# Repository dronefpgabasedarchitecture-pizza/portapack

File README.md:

portapack
=========

Portable software-defined radio add-on for HackRF Jawbreaker

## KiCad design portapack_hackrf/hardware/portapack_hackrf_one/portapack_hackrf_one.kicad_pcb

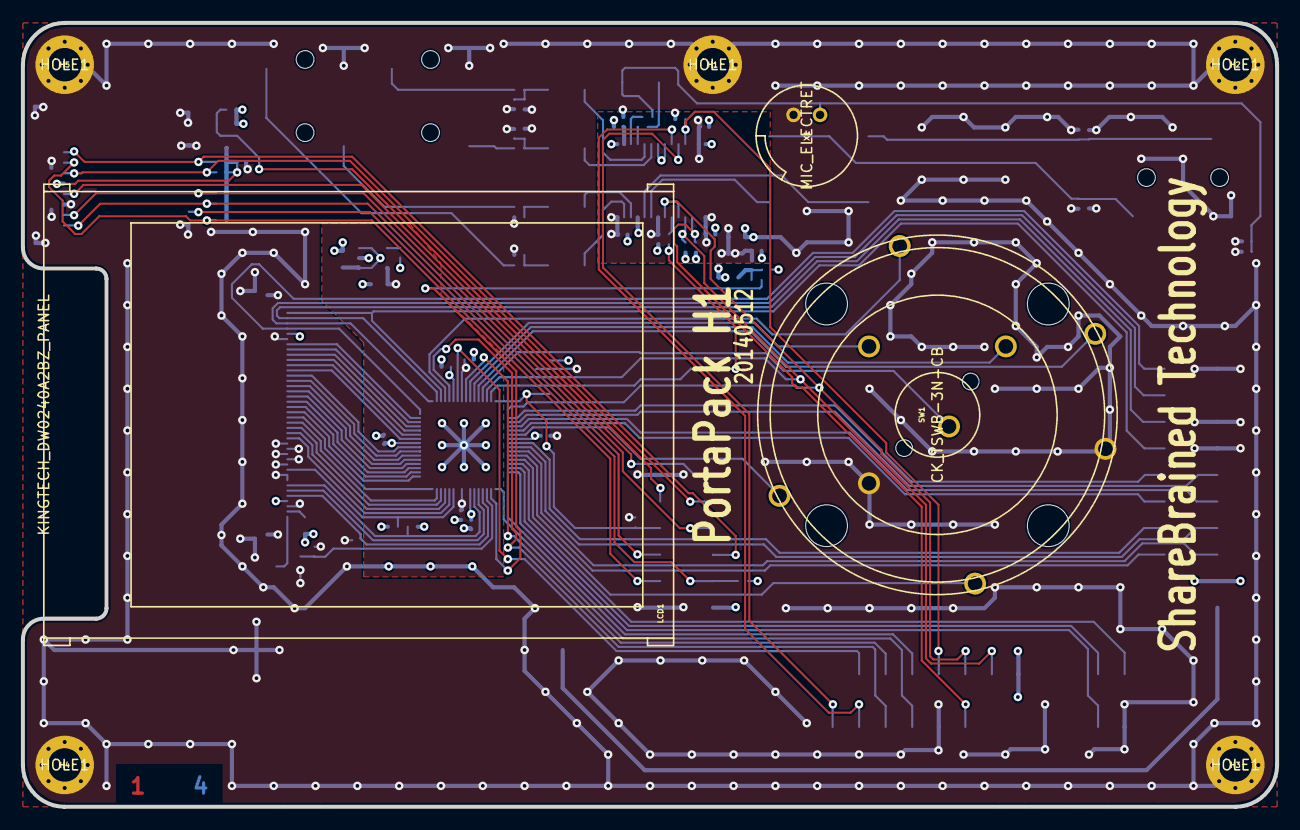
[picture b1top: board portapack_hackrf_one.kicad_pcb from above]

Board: 4 copper layers, 120.0 x 75.0 mm, 92 parts (0 on the bottom side), 100 nets.

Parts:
BT1: BATTERY; MPD_BU2032SM-BT-G
C1, C2: 220U; IPC_CAPAE830X620N
C3, C11, C12: 1U; IPC_CAPAE430X540N
C4, C5, C6, C9, C10: 220P; IPC_CAPC1005X55N
C7, C15, C16, C18, C19, C20, C21, C22, C24, C25, C26, C28, C29, C30: 100N; IPC_CAPC1005X55N
C8, C27: 10U; IPC_CAPC1608X95N
C13, C14: 10U; IPC_CAPAE430X540N
C17: 1U; IPC_CAPC1608X95N
C23: DNI; IPC_CAPC1005X55N
H1, H2, H3, H4, H5: HOLE1; HOLE_3200UM_VIAS
J2: MICROSD_DETSW; ALPS_SCHA4B0400
J3: KINGTECH_DW0240A2BZ_FPC; MOLEX_54132-40XX_LR
LCD1: KINGTECH_DW0240A2BZ_PANEL
P1: TRRS_SW_JACK; CUI_SJ-43516-SMT
P2, P3: TRS_JACK; CUI_SJ-3524-SMT
P20: HACKRF_ONE_P20; HEADER_11X2_REV_SM_254
P22: HACKRF_ONE_P22; HEADER_13X2_REV_SM_254
P28: HACKRF_ONE_P28; HEADER_11X2_REV_SM_254
Q1, Q2: MOSFET_P; IPC_SOT95P240X110-3N
Q3: MOSFET_N; IPC_SOT95P230X110-3N
R1: R; IPC_RESC1005X40N
R2, R3, R4, R17, R18: 47K; IPC_RESC1005X40N
R5: 680R; IPC_RESC1005X40N
R6, R12, R13, R14, R15, R16, R19, R20, R23, R24, R25, R27, R28, R29, R31, R32, R33: 10K; IPC_RESC1005X40N
R7, R8, R10, R11: 5K6; IPC_RESC1005X40N
R9: 100K; IPC_RESC1005X40N
R21, R22, R26: 100R; IPC_RESC1005X40N
R30: R; IPC_RESC1608X55N
SW1: CK_TSWB-3N-CB; CK_TSWB-3N-CB222_LFS
TP1, TP2, TP3, TP4, TP5, TP6: TP; TP_1MM
U1: 5M40ZE64; IPC_QFP40P900X900X120-65N
U2: REGULATOR_SOT23_5; IPC_SOT95P280X110-5N
U3: WM8731SEDS; IPC_SOP65P780X200-28N
X1: MIC_ELECTRET; CUI_CMA-4544PF-W

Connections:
+1.8V: C22.1, C26.1, C27.1, U1.8, U1.41, U2.5
+3.3V: C16.1, C17.1, C18.1, C20.1, C21.1, J3.4, J3.36, P20.3, P22.11, P28.1, Q1.2, Q2.2, R9.1, R13.1, R23.1, R28.1, R29.1, R30.1, TP6.1, U1.6, U1.23, U1.39, U1.57, U2.1, U2.3
/CODEC_ENABLE#: R6.2, U1.34
/CODEC_VDD: C7.1, C8.1, C19.1, C24.2, C25.1, C28.2, Q1.3, R12.1, U3.1, U3.8, U3.14, U3.27
/CPLD_TDI: P28.19, R26.2, TP2.1, U1.15
/GPIO3_8: P20.5, U1.26
/GPIO3_9: P20.6, U1.27
/GPIO3_10: P20.7, U1.25
/GPIO3_11: P20.8, U1.24
/GPIO3_12: P20.9, U1.20
/GPIO3_13: P20.10, U1.21
/GPIO3_14: P20.11, U1.19
/GPIO3_15: P20.12, U1.18
/I2S0_MCLK: P22.17, R31.1, U3.25
/I2S0_RX_SDA: R26.1, U3.6
/I2S0_SCK: P22.16, R24.1, U3.3
/I2S0_TX_SDA: P22.13, R25.1, TP1.1, U1.14, U3.4
/I2S0_WS: P22.15, TP4.1, U1.17, U3.5, U3.7
/LCD_BACKLIGHT: Q3.1, R27.1, U1.35
/LCD_DB0: J3.33, U1.62
/LCD_DB1: J3.32, U1.61
/LCD_DB2: J3.31, U1.60
/LCD_DB3: J3.30, U1.59
/LCD_DB4: J3.29, U1.58
/LCD_DB5: J3.28, U1.56
/LCD_DB6: J3.27, U1.55
/LCD_DB7: J3.26, U1.54
/LCD_DB8: J3.25, U1.53
/LCD_DB9: J3.24, U1.52
/LCD_DB10: J3.23, U1.51
/LCD_DB11: J3.22, U1.50
/LCD_DB12: J3.21, U1.49
/LCD_DB13: J3.20, U1.48
/LCD_DB14: J3.19, U1.47
/LCD_DB15: J3.18, U1.46
/LCD_DB16: J3.17, U1.45
/LCD_DB17: J3.16, U1.44
/LCD_RD#: J3.7, R29.2, U1.38
/LCD_RESET#: J3.5, R33.1, U1.36
/LCD_RS: J3.6, U1.37
/LCD_TE: J3.34, U1.63
/LCD_WR#: J3.10, R28.2, U1.43
/LHPOUT: C1.1, U3.9
/LLINEIN: C11.1, U3.20
/LOUT: C13.1, U3.12
/MICBIAS: C30.1, R5.1, U3.17
/MICIN: R1.2, U3.18
/P1_8: P28.8, R32.1, TP3.1, U1.16
/P2_3: P22.6, U1.31
/P2_4: P22.5, U1.30
/P2_8: P22.23, U1.7
/P2_9: P22.21, U1.9
/P2_13: P22.22, U1.5
/RESET#: P22.3, U1.29
/RHPOUT: C2.1, U3.10
/RLINEIN: C12.1, U3.19
/ROUT: C14.1, U3.13
/SCL: P22.26, U3.24
/SDA: P22.24, U3.23
/SD_CD: J2.A, P28.3, R13.2
/SD_CLK: J2.5, P28.11
/SD_CMD: J2.3, P28.9, R16.2
/SD_DAT0: J2.7, P28.7, R15.2
/SD_DAT1: J2.8, P28.6, R14.2
/SD_DAT2: J2.1, P28.5, R20.2
/SD_DAT3: J2.2, P28.4, R19.2
/SD_POW: P28.10, Q2.1, R23.2
/SW_D: SW1.S2, U1.12
/SW_L: SW1.S5, U1.28
/SW_R: SW1.S3, U1.4
/SW_ROT_A: SW1.A, U1.11
/SW_ROT_B: SW1.B, U1.10
/SW_SEL: SW1.S1, U1.13
/SW_U: SW1.S4, U1.22
/TP_D: J3.38, P20.18, U1.1
/TP_L: J3.39, P20.16, U1.2
/TP_R: J3.37, P20.20, U1.64
/TP_U: J3.40, P20.14, U1.3
/U0_RXD: P22.19, U1.32
/U0_TXD: P22.20, U1.33
/VBAT: BT1.1, P20.1
GND: BT1.2, C4.1, C5.2, C6.2, C8.2, C9.1, C10.2, C15.2, C16.2, C17.2, C18.2, C19.2, C20.2, C21.2, C22.2, C23.2, C24.1, C25.2, C26.2, C27.2, C28.1, C29.2, C30.2, H1.1, H2.1, H3.1, H4.1, H5.1, J2.0, J2.6, J2.B, J2.SH, J3.3, J3.8, J3.9, J3.11, J3.12, J3.13, J3.14, J3.15, J3.35, J3.SHLD, P1.4, P2.1, P3.1, P20.13, P20.15, P20.19, P22.4, P22.10, P22.18, P28.2, P28.12, Q3.2, R2.1, R3.2, R4.2, R10.1, R11.2, R12.2, R17.1, R18.2, R24.2, R25.2, R27.2, R31.2, R32.2, R33.2, SW1.CA, SW1.CB, TP5.1, U1.65, U2.2, U3.11, U3.15, U3.21, U3.22, U3.28, X1.2
unnamed: C1.2, C4.2, P1.2, R2.2
unnamed: C2.2, C5.1, P1.3, R3.1
unnamed: C3.1, R1.1
unnamed: C3.2, C6.1, P1.1, R4.1, R5.2, X1.1
unnamed: C7.2, Q1.1, R6.1, R9.2
unnamed: C10.1, C12.2, R8.1, R11.1
unnamed: C9.2, C11.2, R7.1, R10.2
unnamed: C13.2, R17.2, R21.2
unnamed: C14.2, R18.1, R22.2
unnamed: C15.1, J2.4, Q2.3, R14.1, R15.1, R16.1, R19.1, R20.1
unnamed: C23.1, U2.4
unnamed: C29.1, U3.16
unnamed: J3.1, Q3.3
unnamed: J3.2, R30.2
unnamed: P2.2, R7.2
unnamed: P2.3, R8.2
unnamed: P3.2, R21.1
unnamed: P3.3, R22.1

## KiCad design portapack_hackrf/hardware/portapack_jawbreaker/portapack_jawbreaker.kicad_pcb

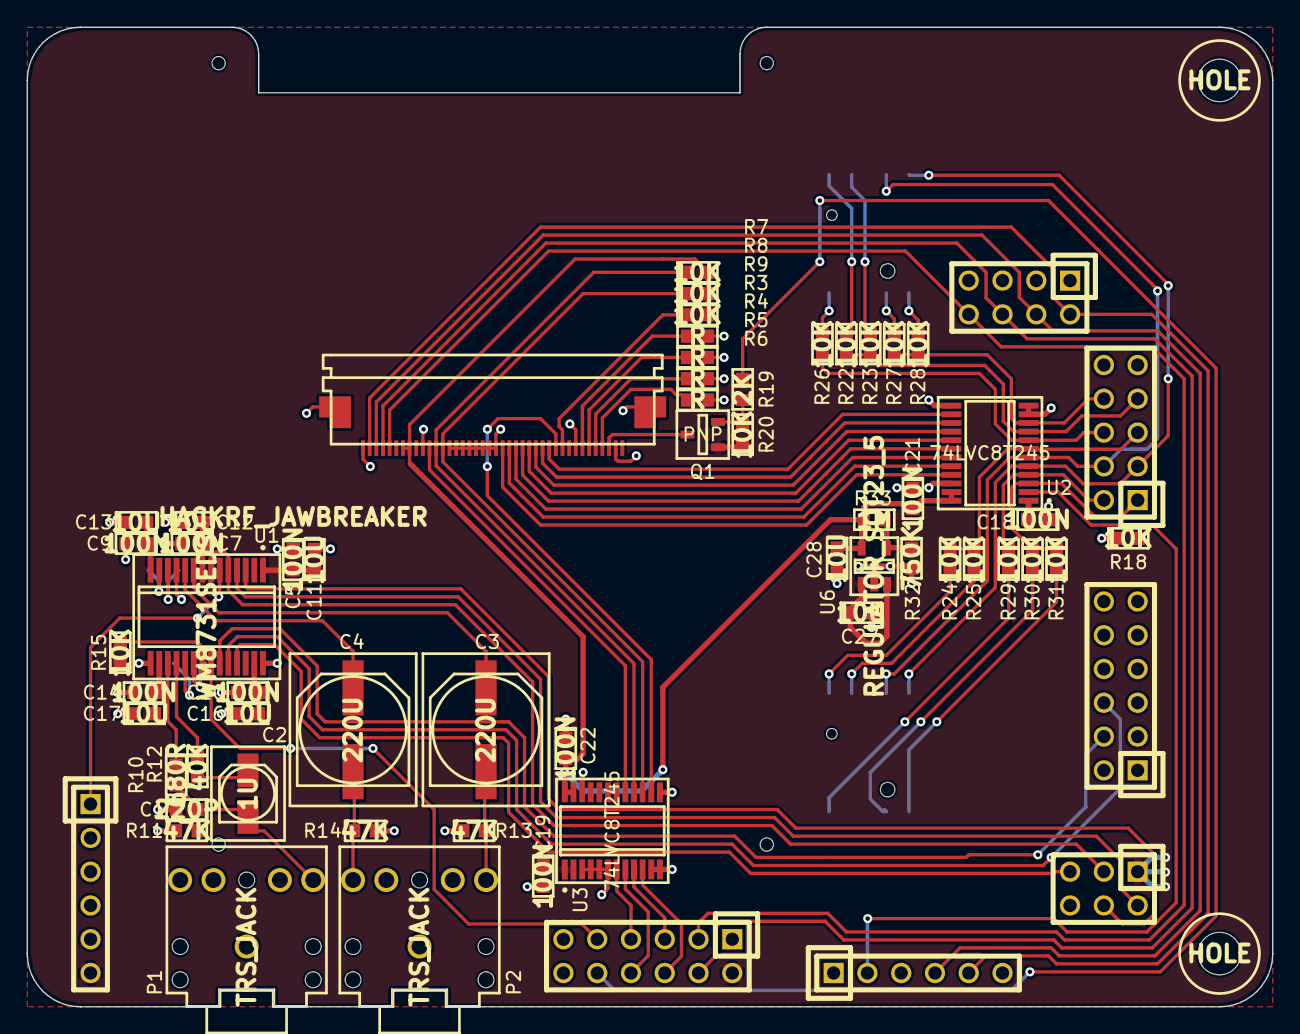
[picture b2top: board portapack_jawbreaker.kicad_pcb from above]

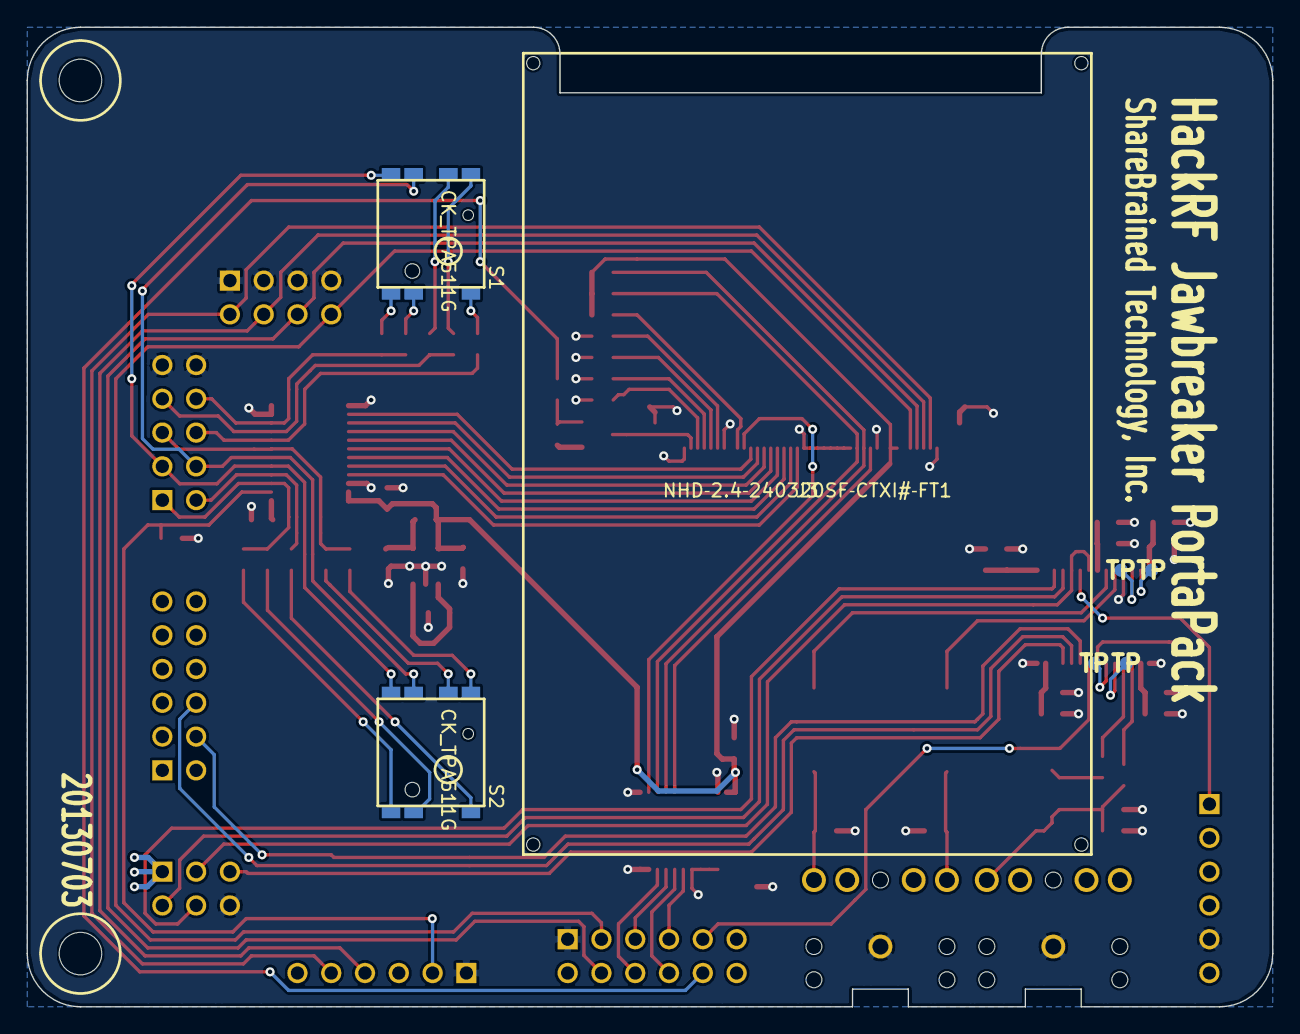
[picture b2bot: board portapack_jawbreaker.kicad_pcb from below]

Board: 2 copper layers, 93.7 x 73.7 mm, 65 parts (7 on the bottom side), 73 nets.

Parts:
C1: 220P; IPC_CAPC1608X90N
C2: 1U; IPC_CAPAE430X540N
C3, C4: 220U; IPC_CAPAE830X620N
C5, C7, C9, C10, C14, C18, C19, C21, C22: 100N; IPC_CAPC1608X90N
C11, C12, C13, C16, C17, C27, C28: 10U; IPC_CAPC1608X95N
H1, H2: HOLE; HOLE_3P2MM
J1: HACKRF_JAWBREAKER; HACKRF_JAWBREAKER_SHIELD
J3: NHD‐2.4‐240320SF‐CTXI#‐FT1; NHD-2.4-240320SF-CTXI-FT1
P1, P2: TRS_JACK; CUI_SJ1-352XN
Q1: PNP; IPC_SOT95P237X111-3N
R3, R4, R5, R6: R; IPC_RESC1608X55N
R7, R8, R9, R15, R18, R20, R22, R23, R24, R25, R26, R27, R28, R29, R30, R31: 10K; IPC_RESC1608X55N
R10: 680R; IPC_RESC1608X55N
R11, R13, R14: 47K; IPC_RESC1608X55N
R12: 40K; IPC_RESC1608X55N
R19: 2K; IPC_RESC1608X55N
R32: 750K; IPC_RESC1608X55N
R33: 1M; IPC_RESC1608X55N
S1, S2: CK_TPA511G
TP1, TP2, TP3, TP4: TP; TP_1MM
U1: WM8731SEDS; IPC_SOP65P780X200-28N
U2, U3: 74LVC8T245; IPC_SOP65P640X120-24N
U6: REGULATOR_SOT23_5; IPC_SOT95P280X110-5N

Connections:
3V3: C5.1, C7.1, C9.1, C10.1, C11.1, C12.1, C13.1, C16.1, C18.1, C19.1, C27.1, J1.2201, J1.2802, J1.2906, Q1.1, R15.2, R20.2, U1.1, U1.8, U1.14, U1.27, U2.1, U3.1, U3.2, U6.1, U6.3
/GPIO0: J1.2001, R30.2, R31.2, U2.3
/GPIO0_S: J3.22, U2.21
/GPIO1: J1.2002, R29.2, U2.4
/GPIO1_S: J3.23, U2.20
/GPIO2: J1.2003, S1.1, S2.1, U2.5
/GPIO2_S: J3.24, U2.19
/GPIO3: J1.2004, S1.2, S2.2, U2.6
/GPIO3_S: J3.25, U2.18
/GPIO4: J1.2005, R24.1, R25.1, U2.7
/GPIO4_S: J3.26, U2.17
/GPIO5: J1.2006, R26.2, U2.8
/GPIO5_S: J3.27, U2.16
/GPIO6: J1.2007, R22.1, R23.1, U2.9
/GPIO6_S: J3.28, U2.15
/GPIO7: J1.2008, R27.2, R28.2, U2.10
/GPIO7_S: J3.29, U2.14
/GPIO_DIR: J1.2502, R18.2, U2.2
/I2S0_RX_SDA: J1.2901, U1.6
/I2S0_TX_MCLK: J1.2205, U1.25
/I2S0_TX_SCK: J1.2204, U1.3
/I2S0_TX_SDA: J1.2202, U1.4
/I2S0_TX_WS: J1.2203, U1.5, U1.7
/LHPOUT: C3.1, U1.9
/MICBIAS: R10.2, U1.17
/MICIN: R12.2, U1.18
/RD#: J1.2805, U3.9
/RD#_S: J3.13, R8.1, U3.15
/RDY#: J1.2810, R19.1
/RESET#: J1.2806, U3.10
/RESET#_S: J3.30, U3.14
/RHPOUT: C4.1, U1.10
/RS: J1.2807, U3.7
/RS_S: J3.11, U3.17
/SPI_CS#_CODEC: J1.2809, U1.22
/SPI_MOSI: J1.1904, U1.23
/SPI_SCK: J1.1906, U1.24
/TS_X+: J1.2104, J1.2504, J3.3
/TS_X-: J1.2108, J1.2803, J3.5
/TS_Y+: J1.2106, J1.2804, J3.4
/TS_Y-: J1.2102, J1.2505, J3.2
/VCC_IO: C21.1, C22.1, C28.1, J3.7, J3.8, R7.2, R8.2, R9.2, R33.2, U2.23, U2.24, U3.23, U3.24, U6.5
/WR#: J1.2808, U3.8
/WR#_S: J3.12, R7.1, U3.16
GND: C1.2, C5.2, C7.2, C9.2, C10.2, C11.2, C12.2, C13.2, C14.2, C16.2, C17.2, C18.2, C19.2, C21.2, C22.2, C27.2, C28.2, J1.2009, J1.2010, J1.2101, J1.2103, J1.2105, J1.2107, J1.2206, J1.2501, J1.2801, J1.2905, J3.1, J3.10, J3.14, J3.15, J3.16, J3.17, J3.18, J3.19, J3.20, J3.21, J3.33, J3.39, J3.SHLD, P1.1, P2.1, R3.1, R4.1, R5.1, R6.1, R11.1, R13.2, R14.1, R18.1, R32.1, U1.11, U1.15, U1.28, U2.11, U2.12, U2.13, U2.22, U3.3, U3.4, U3.5, U3.6, U3.11, U3.12, U3.13, U3.22, U6.2
unnamed: TP3.1, U1.20
unnamed: TP1.1, U1.12
unnamed: TP2.1, U1.13
unnamed: TP4.1, U1.19
unnamed: R28.1, S1.4
unnamed: C1.1, C2.2, P1.2, R10.1, R11.2
unnamed: C2.1, R12.1
unnamed: C3.2, P2.2, R13.1
unnamed: R15.1, U1.21
unnamed: C4.2, P2.3, R14.2
unnamed: J3.31, R9.1
unnamed: C14.1, C17.1, U1.16
unnamed: Q1.2, R19.2, R20.1
unnamed: R31.1, S2.4
unnamed: J3.38, Q1.3
unnamed: R25.2, S2.6
unnamed: R30.1, S2.3
unnamed: R24.2, S2.7
unnamed: R26.1, S1.5
unnamed: R29.1, S2.5
unnamed: R22.2, S1.7
unnamed: R23.2, S1.6
unnamed: R27.1, S1.3
unnamed: R32.2, R33.1, U6.4
unnamed: J3.35, R4.2
unnamed: J3.36, R5.2
unnamed: J3.37, R6.2
unnamed: J3.34, R3.2

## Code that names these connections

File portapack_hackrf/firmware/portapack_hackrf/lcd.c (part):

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#include "lcd.h"
#include "font_fixed_8x16.h"

#define RDY_N_PORT (GPIO1)
#define RDY_N_PIN (8)
#define RDY_N_BIT (1 << RDY_N_PIN)

#define SPI_CS_N_CODEC_PORT (GPIO1)
#define SPI_CS_N_CODEC_PIN (9)
#define SPI_CS_N_CODEC_BIT (1 << SPI_CS_N_CODEC_PIN)

#define WR_N_PORT (GPIO1)
#define WR_N_PIN (1)
#define WR_N_BIT (1 << WR_N_PIN)

#define RS_PORT (GPIO1)
#define RS_PIN (2)
#define RS_BIT (1 << RS_PIN)

#define RESET_N_PORT (GPIO1)
#define RESET_N_PIN (3)
#define RESET_N_BIT (1 << RESET_N_PIN)

#define RD_N_PORT (GPIO1)
#define RD_N_PIN (4)
#define RD_N_BIT (1 << RD_N_PIN)

#define TS_Y_P_PORT (GPIO1)
#define TS_Y_P_PIN (5)
#define TS_Y_P_BIT (1 << TS_Y_P_PIN)

#define TS_X_N_PORT (GPIO1)
#define TS_X_N_PIN (6)
#define TS_X_N_BIT (1 << TS_X_N_PIN)

#define TS_X_P_PORT (GPIO5)
#define TS_X_P_PIN (1)
#define TS_X_P_BIT (1 << TS_X_P_PIN)

#define TS_Y_N_PORT (GPIO5)
#define TS_Y_N_PIN (0)
#define TS_Y_N_BIT (1 << TS_Y_N_PIN)

#define DATA_DIR_PORT (GPIO0)
#define DATA_DIR_PIN (7)
#define DATA_DIR_BIT (1 << DATA_DIR_PIN)

#define DATA_BYTE_PORT (GPIO3)
#define DATA_BYTE_LSB_PIN (8)
#define DATA_BYTE_MASK (0xff << DATA_BYTE_LSB_PIN)

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}

void lcd_dir_read() {
	GPIO_DIR(GPIO3) &= ~(0xffL << 8);
	lcd_dir(0);
}

void lcd_dir_write() {
	lcd_dir(1);
	GPIO_DIR(GPIO3) |= (0xffL << 8);
}

void lcd_dir_idle() {
	lcd_dir(1);
	GPIO_DIR(GPIO3) &= ~(0xffL << 8);
}

void lcd_rs(const uint_fast8_t value) {
	MMIO32(GPIO_W34) = value;
}

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	lcd_dir_read();
	lcd_rd_n(0);
	delay(100);
	const uint_fast8_t value = (GPIO3_PIN >> 8) & 0xff;
	lcd_rd_n(1);
	lcd_dir_idle();
	
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	// Discharge all pins before changing to inputs for reading.
	GPIO3_MPIN = 0 << 8;

	GPIO_DIR(GPIO3) &= ~(0xffL << 8);
	GPIO_DIR(GPIO3) |= (1 << (3 + 8)) | (1 << (2 + 8));

	MMIO32(GPIO_W107) = 0;
	MMIO32(GPIO_W106) = 1;	// GPIO2 reads LEFT/DOWN/SELECT
	delay(100);
	uint32_t data = (GPIO3_MPIN >> 8) & 0xff;
	// GPIO7: S1.DOWN
	// GPIO6: S1.LEFT
	// GPIO5: S1.SELECT
	// GPIO4: S2.LEFT
	// GPIO1: S2.SELECT
	// GPIO0: S2.DOWN

	MMIO32(GPIO_W106) = 0;
	MMIO32(GPIO_W107) = 1;	// GPIO3 reads RIGHT/UP
	delay(100);
	data |= GPIO3_MPIN & 0xff00;
	// GPIO7: S1.UP
	// GPIO6: S1.RIGHT
	// GPIO4: S2.RIGHT
	// GPIO0: S2.UP

	MMIO32(GPIO_W107) = 0;
	
	GPIO_DIR(GPIO3) |= (0xffL << 8);

	return data;
}
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	
	//gpio_set(RDY_N_PORT, RDY_N_PIN);
	lcd_backlight_n(1);
	GPIO_DIR(RDY_N_PORT) |= RDY_N_BIT;
	/*
	gpio_set(SPI_CS_N_CODEC_PORT, SPI_CS_N_CODEC_PIN);
	GPIO_DIR(SPI_CS_N_CODEC_PORT) |= SPI_CS_N_CODEC_BIT;
	*/
	//gpio_set(WR_N_PORT, WR_N_PIN);
	lcd_wr_n(1);
	GPIO_DIR(WR_N_PORT) |= WR_N_BIT;
	
	gpio_clear(RS_PORT, RS_PIN);
	GPIO_DIR(RS_PORT) |= RS_BIT;
	
	//gpio_clear(RESET_N_PORT, RESET_N_PIN);
	lcd_reset_n(0);
	GPIO_DIR(RESET_N_PORT) |= RESET_N_BIT;
	
	//gpio_set(RD_N_PORT, RD_N_PIN);
	lcd_rd_n(1);
	GPIO_DIR(RD_N_PORT) |= RD_N_BIT;
	
	//GPIO_DIR(TS_Y_P_PORT) |= TS_Y_P_BIT;
	//GPIO_DIR(TS_X_N_PORT) |= TS_X_N_BIT;
	
	//scu_pinmux(SCU_PINMUX_CPLD_TMS, (SCU_CONF_FUNCTION3));	// I2S0_RX_SDA
	
	scu_pinmux(SCU_PINMUX_U0_TXD, (SCU_GPIO_NOPULL | SCU_CONF_FUNCTION4));
	scu_pinmux(SCU_PINMUX_U0_RXD, (SCU_GPIO_NOPULL | SCU_CONF_FUNCTION4));
	scu_pinmux(SCU_PINMUX_ISP, (SCU_GPIO_NOPULL | SCU_CONF_FUNCTION0));

	//GPIO_DIR(TS_X_P_PORT) |= TS_X_P_BIT;
	//GPIO_DIR(TS_Y_N_PORT) |= TS_Y_N_BIT;
	
	//gpio_clear(DATA_DIR_PORT, DATA_DIR_PIN);
	lcd_dir_read();
	GPIO3_MASK = ~(0xffU << 8);
	GPIO_DIR(DATA_DIR_PORT) |= DATA_DIR_BIT;
	/*
	scu_pinmux(SCU_PINMUX_I2S0_TX_SDA, (SCU_CONF_FUNCTION0));
	scu_pinmux(SCU_PINMUX_I2S0_TX_WS, (SCU_CONF_FUNCTION0));
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	scu_pinmux(SCU_PINMUX_GPIO3_14, (SCU_GPIO_NOPULL | SCU_CONF_FUNCTION0));
	scu_pinmux(SCU_PINMUX_GPIO3_15, (SCU_GPIO_NOPULL | SCU_CONF_FUNCTION0));
	
	GPIO_DIR(DATA_BYTE_PORT) &= ~(DATA_BYTE_MASK);
	/*
	scu_pinmux(SCU_SSP0_SCK, (SCU_CONF_FUNCTION1));		// SPI
	scu_pinmux(SCU_SSP0_MOSI, (SCU_CONF_FUNCTION1));	// SPI	
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
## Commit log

2014-01-01 Committed 20130703_1525 schematic/PCB/Gerbers of Jawbreaker PortaPack.
2014-01-01 HackRF PortaPack code in progress. Remnants of the spectrum analyzer code and VFD code are present and need a better home.
2014-01-01 Basic .gitignore.
2014-01-01 Fix breakage from incomplete change in decimation and demodulation API arguments.
2014-01-01 Finish/unbreak change to processing loop metrics variable names.
2014-01-01 Remove unused variable.
2014-01-01 Disable unfinished narrowband FM processing function.
2014-01-01 Document WBFM audio filter/decimator.
2014-01-01 Clean up call arguments within FM broadcast demodulation function.
2014-01-01 Add TODO to implement FM broadcast channel filter for improved adjacent channel rejection.
2014-01-01 Clean up comments in baseband processing.
2014-01-01 Clean up decimation API arguments.
2014-01-01 Move decimation functions into decimate.*. Clean up decimation APIs a bit more. Remove junk decimation functions.
2014-01-01 Quick and dirty NBFM receive support. Receives NOAA WX radio well, but could certainly use a channel filter and other tweaks.
2014-01-01 Remove dead code/comment.
2014-01-01 Remove a bit more dead code. I'm committed to using the fixed-point atan2() at this point.
2014-01-01 Extract a few complex math functions.
2014-01-01 Remove gr_fast_atan2f from code. TODO to implement FM demodulation gain correction.
2014-01-01 Clean up and rename demodulation APIs a bit more.
2014-01-01 Add AM receiver code.
2014-01-01 More decimation function renaming...
2014-01-01 Generalize FIR real filter a bit, extract filter taps into application code.
2014-01-01 Massive rework of LCD layer, refactored a bunch of stuff.
2014-01-02 Define some color constants.
2014-01-02 Reformat default color values to be a bit more verbose.
2014-01-02 Fix LCD font pixel scan order.
2014-01-02 Add function to compute string pixel width based on current font.
2014-01-02 Tweak lcd_draw_string() to support variable-width characters in a font.
2014-01-02 Nuke residual spectrum analyzer code that will need serious upgrading to work with new frameworks.
2014-01-02 Add bigger, 8x16 fixed font, make the default.
2014-01-02 Clean up application tuning functions.
2014-01-02 Add LCD field drawing functions.
2014-01-02 Relocate baseband sample buffers to make a 32K block for the M0. Relocate shared memory items to new M0 region.
2014-01-02 Create device_state structure to share data between M4 and M0 processors.
2014-01-02 Re-plumb application code to use device_state values.
2014-01-02 Temporary delay() fix to slow down main loop so that buttons and switches don't react/repeat way too fast...
2014-01-02 Rework LCD data to take use of the new font, field rendering, and device state.
2014-01-02 Add and use LCD color invert function.
2014-01-02 Fix MHz field display to drop <kHz digits.
2014-01-02 Fix percent field display to show only 1/10% precision.
2014-01-02 Extract cycles renderer into separate function.
2014-01-02 Uncomment lcd_data_read().
2014-01-02 Add lcd_get_scanline(), helpful to sync with LCD refresh.
2014-01-02 Missing argument in draw_cycles().
2014-01-02 Add LCD refresh synchronization and frame counter (mostly for validation).
2014-01-02 Move application-specific tuning stuff out of spectrum.[ch], into spectrum_lcd.c.
2014-01-02 Clear out portapack.[ch] in preparation for spectrum_lcd.c moving into its place.
2014-01-02 Remove LED toggle in GPDMA ISR.
2014-01-02 Clean up #includes.
2014-01-02 Makefile clean-up, removed extraneous .o files, VFD-specific build.
2014-01-02 Remove VFD-specific code.
2014-01-03 Add ARM intrinsics for SEV, WFE, WFI instructions.
2014-01-03 Enable M0APPTXEVENT interrupt on M4. Handle M0 interrupt on M4, checking value to execute UI commands from M0. Move the joysticks handler to the M0. Replace M4 main loop with a WFE (processor sleep a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
2014-01-03 Remove GPIO toggling in M0 (UI) main loop.
2014-01-04 Tweak event and sleep ARM intrinsics to indicate they change memory.
2014-01-04 Add isb, dsb, dmb ARM intrinsics.
2014-01-04 Add Linux kfifo implementation, rejiggered to work on embedded platforms without user/kernel memory distinction, memory alloc/free, DMA support, etc. Also bring in required bits from Linux #include h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
2014-01-04 Remove min() definition, replace with Linux min() in linux_stuff.h.
2014-01-04 Remove now-unused #includes.
2014-01-04 Simple IPC mechanism for M0 UI requesting RF/DSP operations from M4 core.
2014-01-04 Adapt UI and DSP code to use IPC for RF/DSP operations. Rework set_frequency() to return success from set_freq(), not do its own frequency range test..
2014-01-04 Fix lcd_dir_idle() to not drive the data bus at all. Previously, the LCD was driving the bus -- same as "read" mode.
2014-01-04 Un-expose switches_state, make it local to the UI code.
2014-01-04 Simple debouncing and edge-detection of switches, so that UI operates and human speed. ;-)
2014-01-05 Add simple UI field structures and list. Rename UI data drawing functions, reuse code in field rendering functions.
2014-01-05 Simple UI navigation and field editing scheme.
2014-01-05 Added IPC commands to change RF and baseband gain. Added UI handlers for RF and baseband gain adjustment.
2014-01-05 Fix copy-and-paste oops preventing right navigation from working.
2014-01-05 Add IPC to set audio output gain.
2014-01-05 Set audio codec initialized volume to -120 dB (or as close as practical).
2014-01-05 Return effective audio out gain value when changing it.
2014-01-05 Add audio output volume field to UI. Add handling of audio out gain to DSP side (TODO: probably not the right place for it long-term).
2014-01-06 Rename UI frame counter, extract from function.
2014-01-06 Change LCD header text a bit.
2014-01-06 Separate switch events into three separate variables: switch on, switch transition to on, switch transition to off.
2014-01-06 Simple up/down key repeat for changing values in UI. Needs refactoring -- too much repeated code. And maybe a field-specific increment rate handler, so the frequency field repeat magnitude can accele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
2014-01-06 Create a struct for UI switch state, refactor switch repeat code.
2014-01-06 Extract lcd_frame_sync(), make note of how lame it is.
2014-01-07 Alter data provided to switch/UI event handlers to indicate the count of repeats, for implementing accelerating repeats. Created a somewhat awkward accelerating frequency behavior.
2014-01-07 Change repeat delay and pace, I'm getting impatient...
2014-01-07 Silence unused argument warnings in handlers.
2014-01-10 Add IPC command to set receiver mode. Render receiver mode to UI, incorporate into navigation, allow selecting among the three options. Remove static receiver mode state variables, use a shared buffe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
2014-01-10 Missing code to load/start M0 from M4 core. (Moved from HackRF to PortaPack.)
2014-05-01 Add lcd_draw_char().
2014-05-01 Remove USB-related code from PortaPack firmware. Leave that to the bootloader and standard HackRF firmware.
2014-05-01 Add RBIT, set_MSP intrinsics.
2014-05-29 Initial build of the PortaPack for HackRF One.

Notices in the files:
portapack_hackrf/firmware/portapack_hackrf/lcd.c:
Copyright (C) 2013 Jared Boone, ShareBrained Technology, Inc.
This program is free software; you can redistribute it and/or modify
it under the terms of the GNU General Public License as published by
the Free Software Foundation; either version 2, or (at your option)
